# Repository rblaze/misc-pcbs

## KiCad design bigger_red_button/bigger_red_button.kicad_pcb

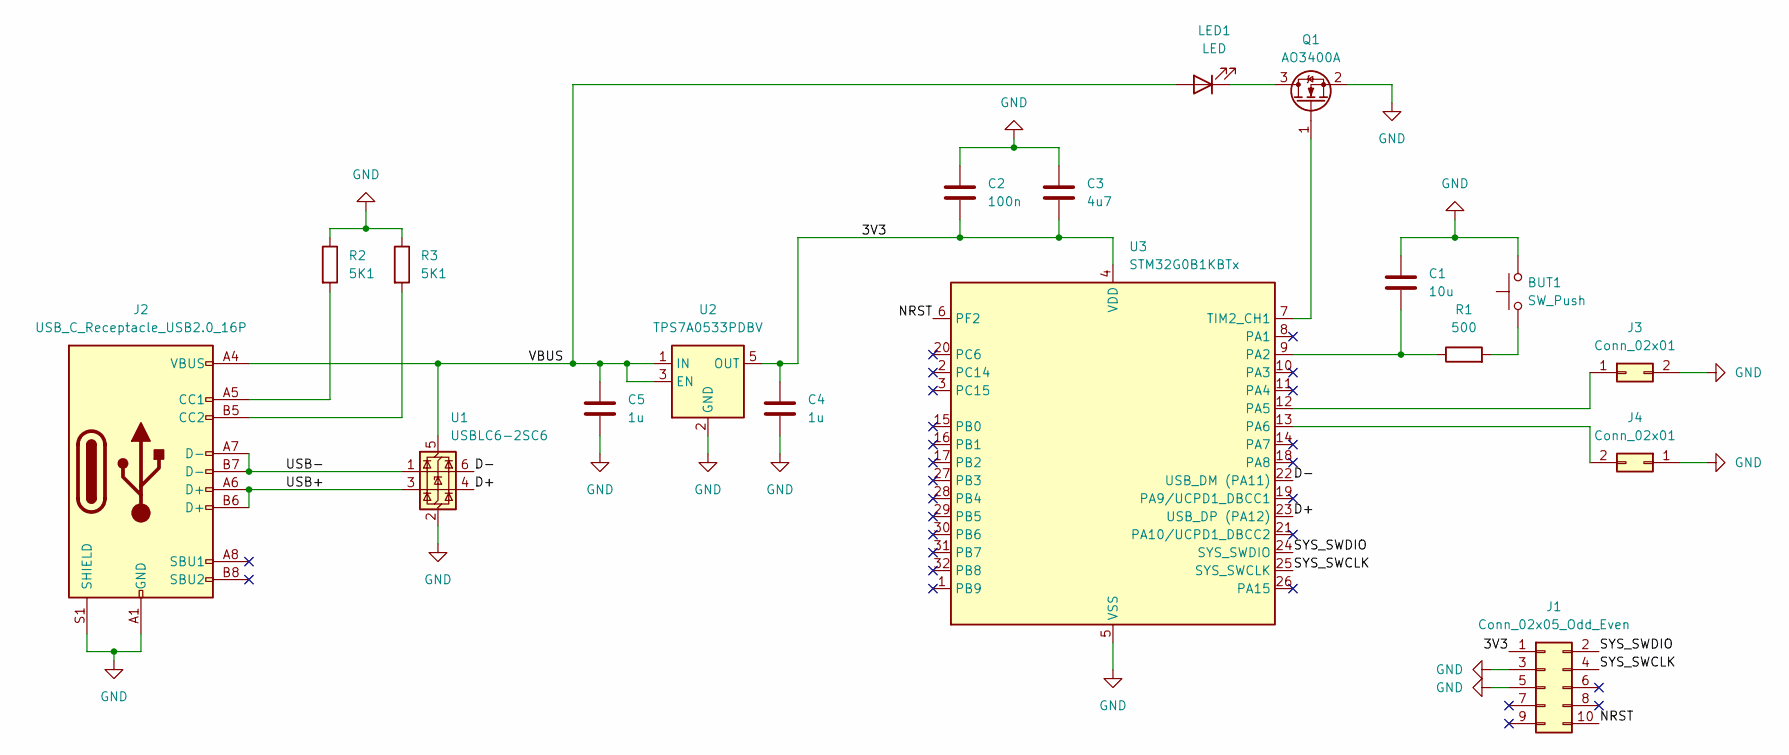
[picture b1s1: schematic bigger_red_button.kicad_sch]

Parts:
BUT1: SW_Push; PinHeader_1x02_P2.54mm_Vertical
C1: 10u; C_0402_1005Metric; LCSC Part # C15525
C2: 100n; C_0402_1005Metric; LCSC Part # C1525
C3: 4u7; C_0402_1005Metric; LCSC Part # C23733
C4, C5: 1u; C_0402_1005Metric; LCSC Part # C52923
J1: Conn_02x05_Odd_Even; SAMTEC_FTSH-105-XX-X-DV; LCSC Part # C448647
J2: USB_C_Receptacle_USB2.0_16P; USB_C_Receptacle_GCT_USB4105-xx-A_16P_TopMnt_Horizontal; LCSC Part # C165948
J3, J4: Conn_02x01; PinHeader_1x02_P2.54mm_Vertical
LED1: LED; PinHeader_1x02_P2.54mm_Vertical
Q1: AO3400A; SOT-23; LCSC Part # C22469448
R1: 500; R_0402_1005Metric; LCSC Part # C25123
R2, R3: 5K1; R_0402_1005Metric; LCSC Part # C25905
U1: USBLC6-2SC6; SOT-23-6; LCSC Part # C7519
U2: TPS7A0533PDBV; SOT-23-5; LCSC Part # C2862740
U3: STM32G0B1KBTx; LQFP-32_7x7mm_P0.8mm; LCSC Part # C3223248

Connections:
/3V3: C2.2, C3.2, C4.1, J1.1, U2.5 (OUT), U3.4 (VDD)
/D+: U1.4 (I/O2), U3.23 (USB_DP (PA12))
/D-: U1.6 (I/O1), U3.22 (USB_DM (PA11))
/NRST: J1.10, U3.6 (PF2)
/SYS_SWCLK: J1.4, U3.25 (SYS_SWCLK)
/SYS_SWDIO: J1.2, U3.24 (SYS_SWDIO)
/USB+: J2.A6 (D+), J2.B6 (D+), U1.3 (I/O2)
/USB-: J2.A7 (D-), J2.B7 (D-), U1.1 (I/O1)
/VBUS: C5.1, J2.A4 (VBUS), J2.A9 (VBUS), J2.B4 (VBUS), J2.B9 (VBUS), LED1.2 (A), U1.5 (VBUS), U2.1 (IN), U2.3 (EN)
GND: BUT1.2, C1.1, C2.1, C3.1, C4.2, C5.2, J1.3, J1.5, J2.A1 (GND), J2.A12 (GND), J2.B1 (GND), J2.B12 (GND), J2.S1 (SHIELD), J3.2, J4.1, Q1.2 (S), R2.1, R3.1, U1.2 (GND), U2.2 (GND), U3.5 (VSS)
unnamed: BUT1.1, R1.2
unnamed: J2.A5 (CC1), R2.2
unnamed: J2.B5 (CC2), R3.2
unnamed: J3.1, U3.12 (PA5)
unnamed: J4.2, U3.13 (PA6)
unnamed: LED1.1 (K), Q1.3 (D)
unnamed: Q1.1 (G), U3.7 (TIM2_CH1)
unnamed: C1.2, R1.1, U3.9 (PA2)

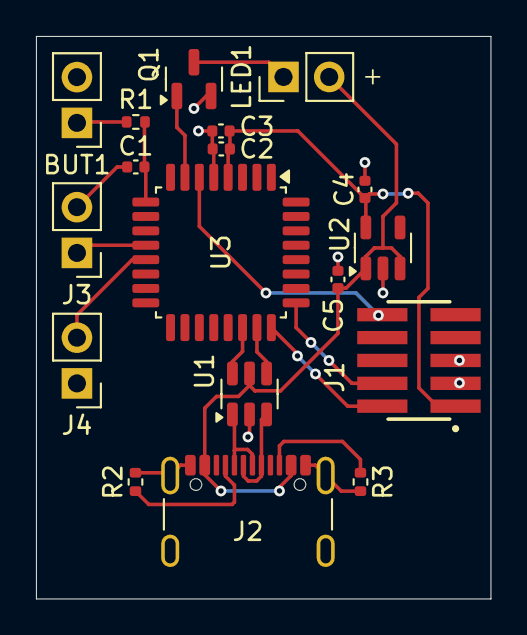
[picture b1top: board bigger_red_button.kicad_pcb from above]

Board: 2 copper layers, 25.2 x 31.2 mm, 18 parts (0 on the bottom side), 18 nets.

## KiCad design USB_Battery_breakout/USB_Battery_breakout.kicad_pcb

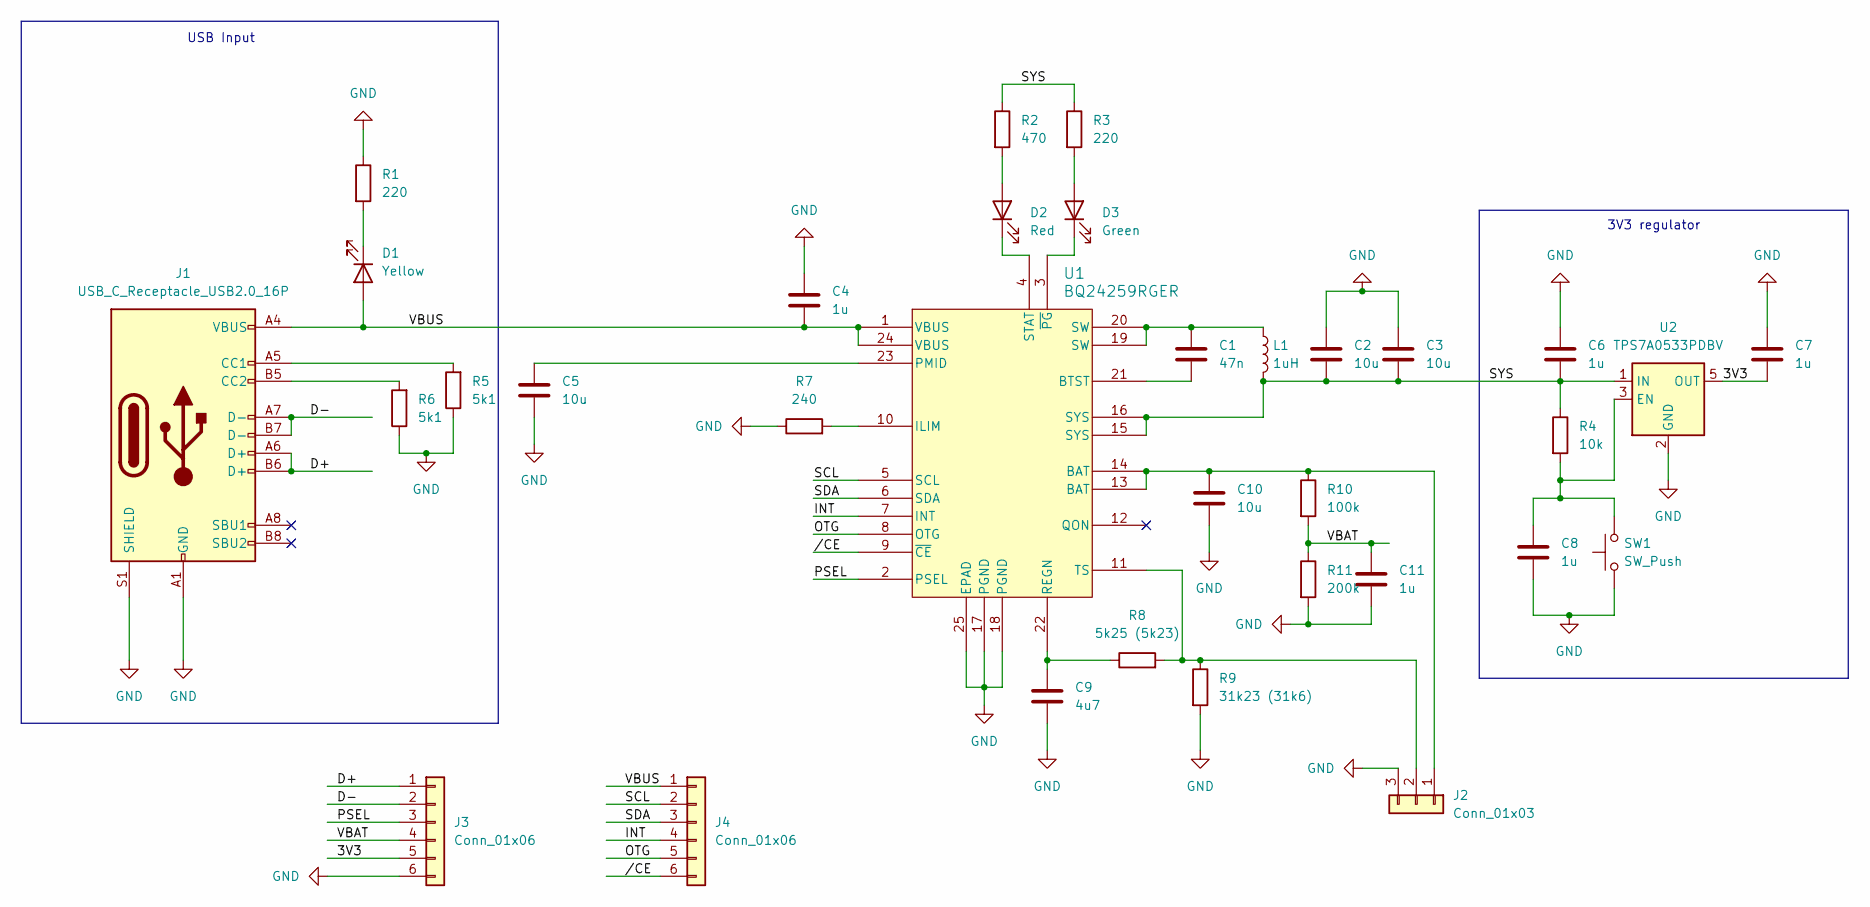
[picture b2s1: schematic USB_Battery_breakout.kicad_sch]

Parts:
C1: 47n; C_0402_1005Metric; JLCPCB C5142571
C2, C3, C5, C10: 10u; C_0603_1608Metric; JLCPCB C19702
C4, C6, C7, C8, C11: 1u; C_0402_1005Metric; JLCPCB C52923
C9: 4u7; C_0402_1005Metric; JLCPCB C23733
D1: Yellow; LED_0603_1608Metric; JLCPCB C72038
D2: Red; LED_0603_1608Metric; JLCPCB C2286
D3: Green; LED_0603_1608Metric; JLCPCB C72043
J1: USB_C_Receptacle_USB2.0_16P; USB_C_Receptacle_GCT_USB4105-xx-A_16P_TopMnt_Horizontal; JLCPCB C165948
J2: Conn_01x03; JST_PH_S3B-PH-SM4-TB_1x03-1MP_P2.00mm_Horizontal
J3, J4: Conn_01x06; PinHeader_1x06_P2.54mm_Vertical
L1: 1uH; L_Murata_DFE201610P; JLCPCB C161082
R1, R3: 220; R_0402_1005Metric; JLCPCB C25091
R2: 470; R_0402_1005Metric; JLCPCB C25117
R4: 10k; R_0402_1005Metric; JLCPCB C25744
R5, R6: 5k1; R_0402_1005Metric; JLCPCB C25905
R7: 240; R_0402_1005Metric; JLCPCB C25091
R8: 5k25 (5k23); R_0402_1005Metric; JLCPCB C852857
R9: 31k23 (31k6); R_0402_1005Metric; JLCPCB C852720
R10: 100k; R_0402_1005Metric; JLCPCB C25741
R11: 200k; R_0402_1005Metric; JLCPCB C25764
SW1: SW_Push; SW_SPST_PTS810
U1: BQ24259RGER; RGE24_2P7X2P7_TEX; JLCPCB C473366
U2: TPS7A0533PDBV; SOT-23-5; JLCPCB C2862740

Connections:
/3V3: C7.2, J3.5, U2.5 (OUT)
/D+: J1.A6 (D+), J1.B6 (D+), J3.1
/D-: J1.A7 (D-), J1.B7 (D-), J3.2
/INT: J4.4, U1.7 (INT)
/OTG: J4.5, U1.8 (OTG)
/PSEL: J3.3, U1.2 (PSEL)
/SCL: J4.2, U1.5 (SCL)
/SDA: J4.3, U1.6 (SDA)
/SYS: C2.2, C3.2, C6.2, L1.2, R2.1, R3.1, R4.1, U1.15 (SYS), U1.16 (SYS), U2.1 (IN)
/VBAT: C11.1, J3.4, R10.2, R11.1
/VBUS: C4.2, D1.2 (A), J1.A4 (VBUS), J1.A9 (VBUS), J1.B4 (VBUS), J1.B9 (VBUS), J4.1, U1.1 (VBUS), U1.24 (VBUS)
//CE: J4.6, U1.9 (~CE)
GND: C2.1, C3.1, C4.1, C5.2, C6.1, C7.1, C8.2, C9.2, C10.2, C11.2, J1.A1 (GND), J1.A12 (GND), J1.B1 (GND), J1.B12 (GND), J1.S1 (SHIELD), J2.3, J3.6, R1.1, R5.1, R6.1, R7.1, R9.2, R11.2, SW1.1, U1.17 (PGND), U1.18 (PGND), U1.25 (EPAD), U1.V, U2.2 (GND)
unnamed: C1.1, L1.1, U1.19 (SW), U1.20 (SW)
unnamed: D1.1 (K), R1.2
unnamed: D2.2 (A), R2.2
unnamed: D2.1 (K), U1.4 (STAT)
unnamed: D3.2 (A), R3.2
unnamed: D3.1 (K), U1.3 (~PG)
unnamed: J1.A5 (CC1), R5.2
unnamed: J1.B5 (CC2), R6.2
unnamed: C10.1, J2.1, R10.1, U1.13 (BAT), U1.14 (BAT)
unnamed: J2.2, R8.2, R9.1, U1.11 (TS)
unnamed: C1.2, U1.21 (BTST)
unnamed: R7.2, U1.10 (ILIM)
unnamed: C5.1, U1.23 (PMID)
unnamed: C9.1, R8.1, U1.22 (REGN)
unnamed: C8.1, R4.2, SW1.2, U2.3 (EN)

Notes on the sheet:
USB Input
3V3 regulator

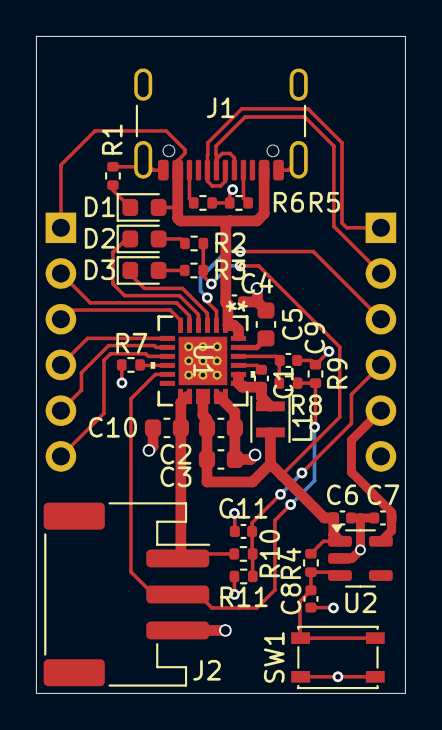
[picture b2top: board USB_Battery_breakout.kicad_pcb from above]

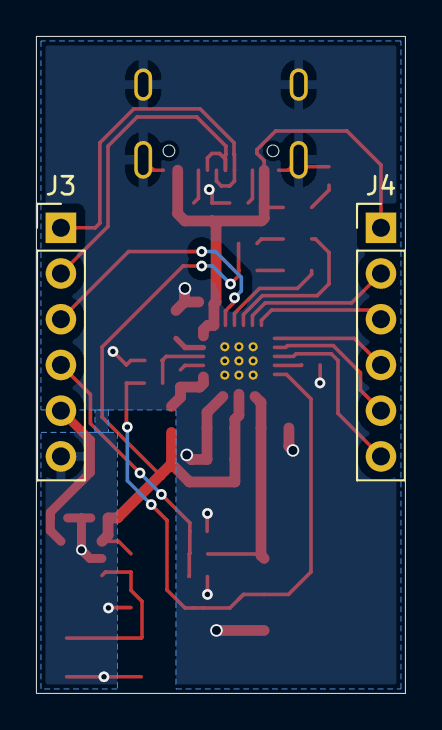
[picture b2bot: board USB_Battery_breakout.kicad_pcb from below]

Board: 2 copper layers, 20.5 x 36.5 mm, 33 parts (2 on the bottom side), 28 nets.

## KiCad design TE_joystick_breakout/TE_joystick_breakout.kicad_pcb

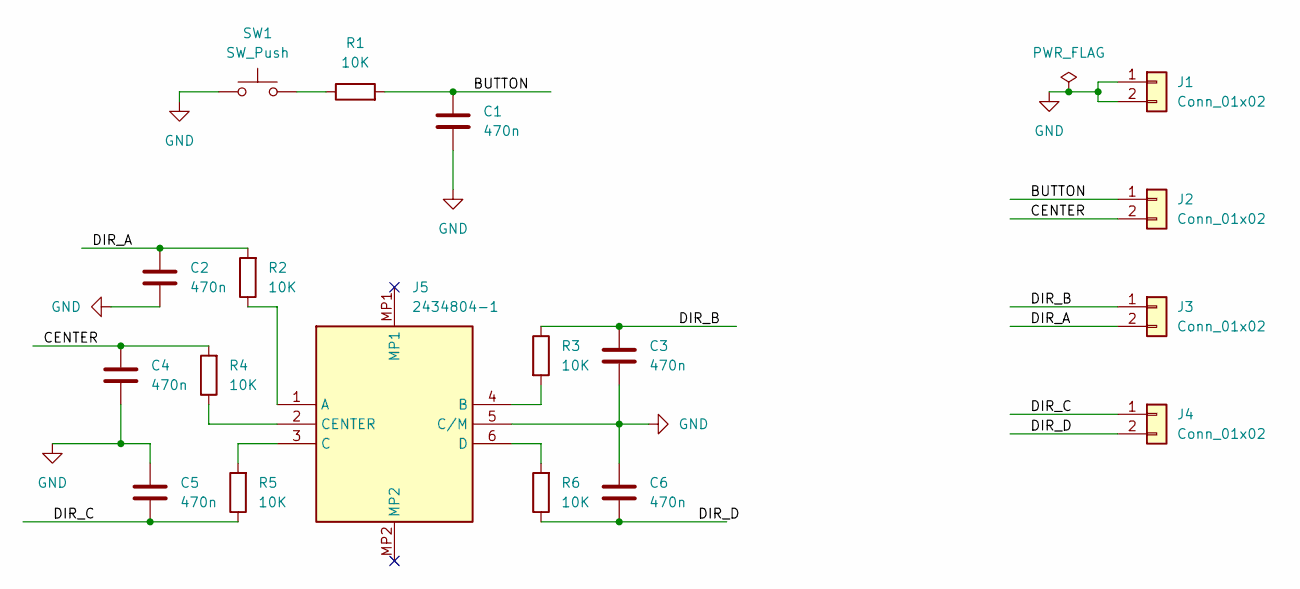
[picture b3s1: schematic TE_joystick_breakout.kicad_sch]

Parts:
C1, C2, C3, C4, C5, C6: 470n; C_0402_1005Metric
J1, J2, J3, J4: Conn_01x02; PinHeader_1x02_P2.54mm_Vertical
J5: 2434804-1; TE_24348041; Manufacturer_Part_Number 2434804-1
R1, R2, R3, R4, R5, R6: 10K; R_0402_1005Metric
SW1: SW_Push; SW_SPST_PTS810

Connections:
/BUTTON: C1.1, J2.1, R1.2
/CENTER: C4.2, J2.2, R4.2
/DIR_A: C2.2, J3.2, R2.2
/DIR_B: C3.2, J3.1, R3.1
/DIR_C: C5.1, J4.1, R5.1
/DIR_D: C6.1, J4.2, R6.1
GND: C1.2, C2.1, C3.1, C4.1, C5.2, C6.2, J1.1, J1.2, J5.5 (C/M), SW1.1
unnamed: J5.1 (A), R2.1
unnamed: J5.4 (B), R3.2
unnamed: J5.3 (C), R5.2
unnamed: J5.2 (CENTER), R4.1
unnamed: J5.6 (D), R6.2
unnamed: R1.1, SW1.2

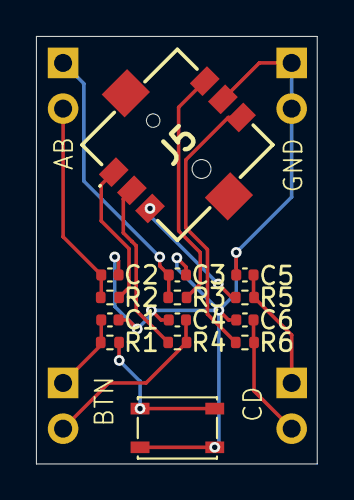
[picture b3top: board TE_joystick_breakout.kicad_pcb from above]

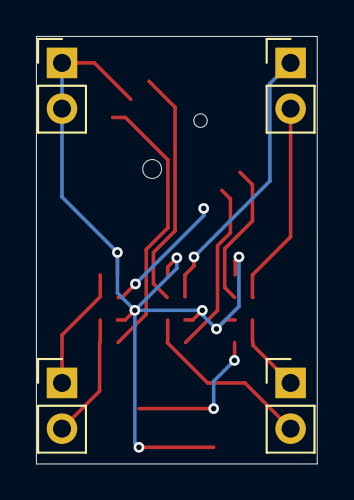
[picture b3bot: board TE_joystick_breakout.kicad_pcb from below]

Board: 2 copper layers, 15.6 x 23.8 mm, 18 parts (4 on the bottom side), 13 nets.

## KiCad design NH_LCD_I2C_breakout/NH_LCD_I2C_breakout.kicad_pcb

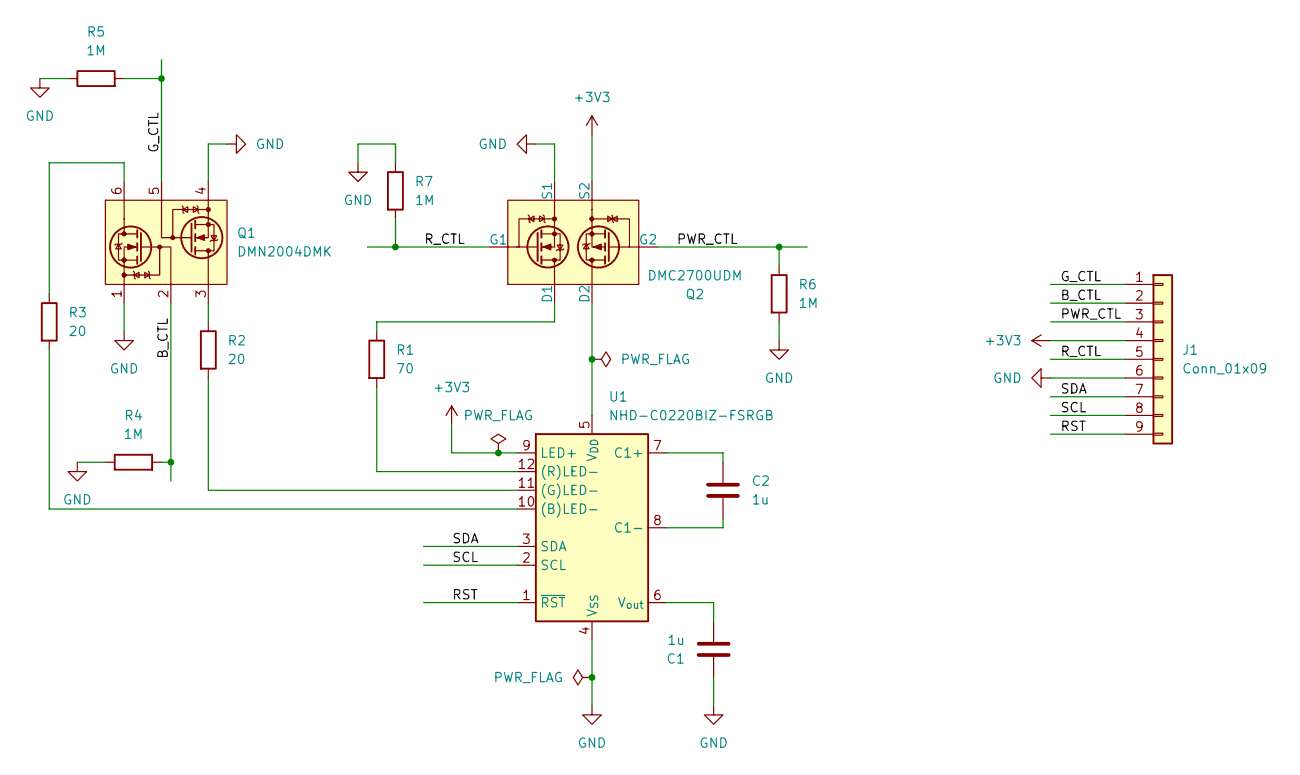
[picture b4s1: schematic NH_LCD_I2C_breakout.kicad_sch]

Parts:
C1, C2: 1u; C_0402_1005Metric
J1: Conn_01x09; PinHeader_1x09_P2.54mm_Vertical
Q1: DMN2004DMK; SOT-23-6
Q2: DMC2700UDM; SOT-23-6
R1: 70; R_0402_1005Metric
R2, R3: 20; R_0402_1005Metric
R4, R5, R6, R7: 1M; R_0402_1005Metric
U1: NHD-C0220BIZ-FSRGB; NHD-C0220BiZ-FSRGB

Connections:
+3V3: J1.4, Q2.2 (S2), U1.9 (LED+)
/B_CTL: J1.2, Q1.2 (G1), R4.2
/G_CTL: J1.1, Q1.5 (G2), R5.2
/PWR_CTL: J1.3, Q2.3 (G2), R6.1
/RST: J1.9, U1.1 (~RST)
/R_CTL: J1.5, Q2.1 (G1), R7.2
/SCL: J1.8, U1.2 (SCL)
/SDA: J1.7, U1.3 (SDA)
GND: C1.1, J1.6, Q1.1 (S1), Q1.4 (S2), Q2.5 (S1), R4.1, R5.1, R6.2, R7.1, U1.4 (V_{SS})
unnamed: Q1.6 (D1), R3.1
unnamed: Q1.3 (D2), R2.1
unnamed: Q2.6 (D1), R1.1
unnamed: Q2.4 (D2), U1.5 (V_{DD})
unnamed: R3.2, U1.10 ((B)LED-)
unnamed: R2.2, U1.11 ((G)LED-)
unnamed: R1.2, U1.12 ((R)LED-)
unnamed: C2.1, U1.7 (C1+)
unnamed: C2.2, U1.8 (C1-)
unnamed: C1.2, U1.6 (V_{out})

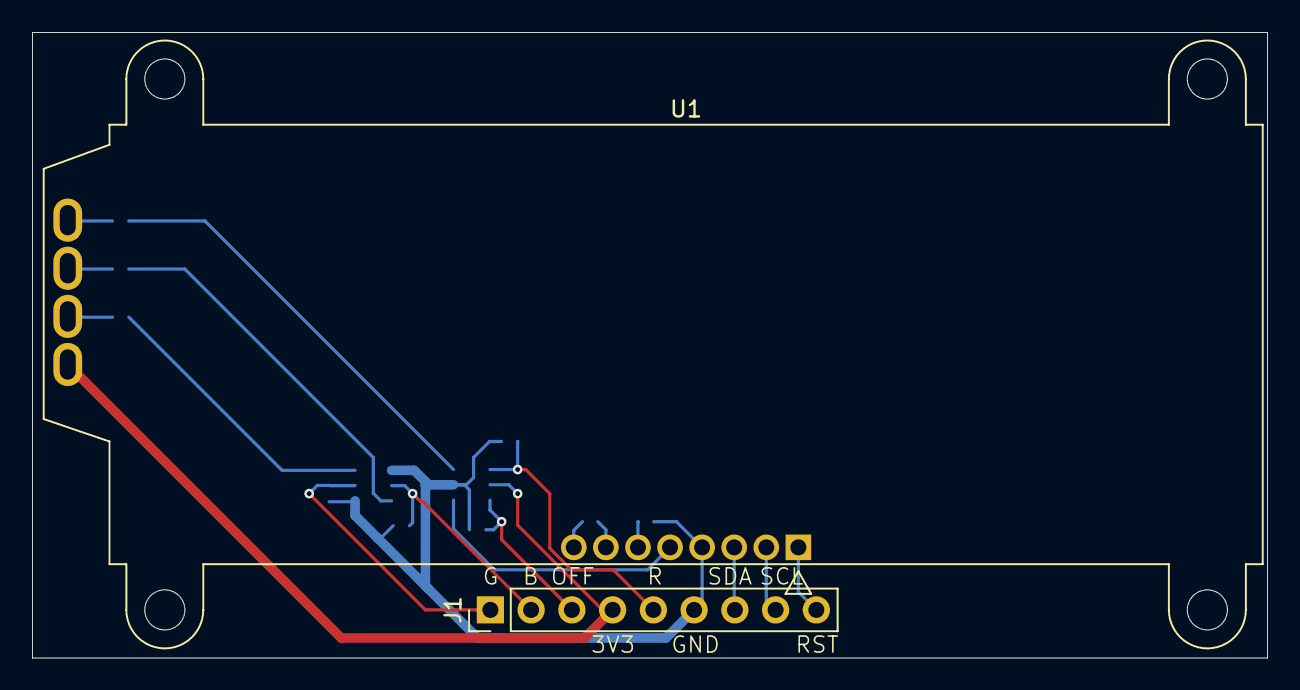
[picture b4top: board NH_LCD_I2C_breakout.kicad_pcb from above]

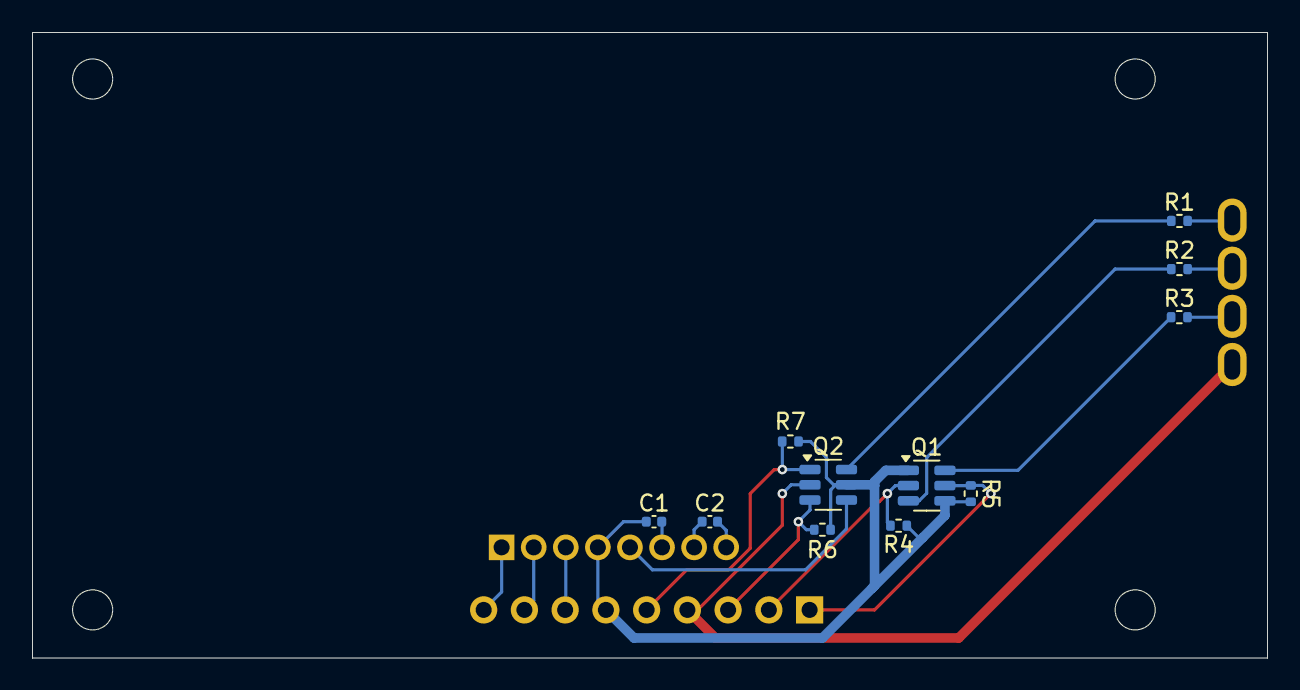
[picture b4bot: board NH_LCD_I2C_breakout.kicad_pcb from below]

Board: 2 copper layers, 77.0 x 39.0 mm, 13 parts (11 on the bottom side), 19 nets.

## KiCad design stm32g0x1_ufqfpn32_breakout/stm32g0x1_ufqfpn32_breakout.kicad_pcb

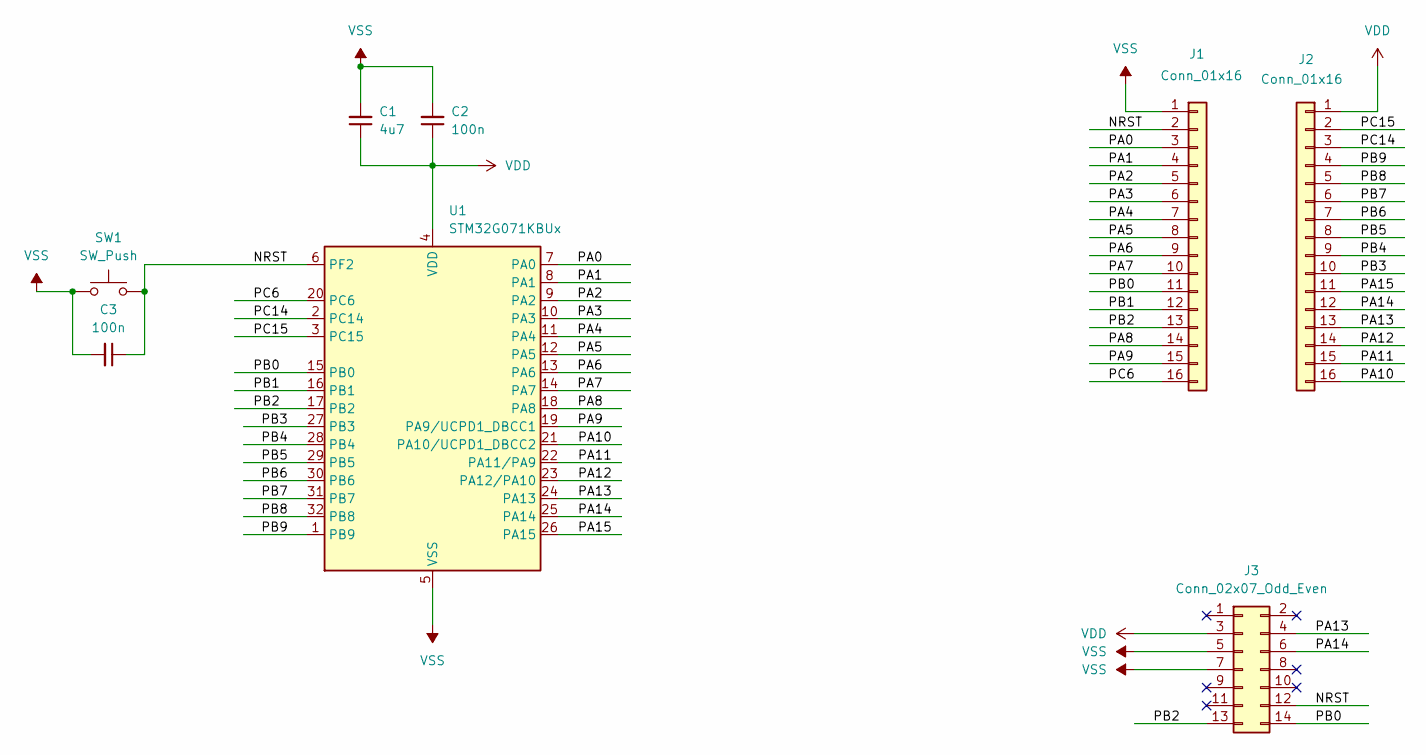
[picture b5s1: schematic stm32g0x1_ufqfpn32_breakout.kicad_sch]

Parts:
C1: 4u7; C_0402_1005Metric
C2, C3: 100n; C_0402_1005Metric
J1, J2: Conn_01x16; PinHeader_1x16_P2.54mm_Vertical
J3: Conn_02x07_Odd_Even; SAMTEC_FTSH-107-01-L-DV-K-A
SW1: SW_Push; SW_SPST_PTS810
U1: STM32G071KBUx; QFN-32-1EP_5x5mm_P0.5mm_EP3.45x3.45mm

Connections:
/NRST: C3.1, J1.2, J3.12, SW1.2, U1.6 (PF2)
/PA0: J1.3, U1.7 (PA0)
/PA1: J1.4, U1.8 (PA1)
/PA2: J1.5, U1.9 (PA2)
/PA3: J1.6, U1.10 (PA3)
/PA4: J1.7, U1.11 (PA4)
/PA5: J1.8, U1.12 (PA5)
/PA6: J1.9, U1.13 (PA6)
/PA7: J1.10, U1.14 (PA7)
/PA8: J1.14, U1.18 (PA8)
/PA9: J1.15, U1.19 (PA9/UCPD1_DBCC1)
/PA10: J2.16, U1.21 (PA10/UCPD1_DBCC2)
/PA11: J2.15, U1.22 (PA11/PA9)
/PA12: J2.14, U1.23 (PA12/PA10)
/PA13: J2.13, J3.4, U1.24 (PA13)
/PA14: J2.12, J3.6, U1.25 (PA14)
/PA15: J2.11, U1.26 (PA15)
/PB0: J1.11, J3.14, U1.15 (PB0)
/PB1: J1.12, U1.16 (PB1)
/PB2: J1.13, J3.13, U1.17 (PB2)
/PB3: J2.10, U1.27 (PB3)
/PB4: J2.9, U1.28 (PB4)
/PB5: J2.8, U1.29 (PB5)
/PB6: J2.7, U1.30 (PB6)
/PB7: J2.6, U1.31 (PB7)
/PB8: J2.5, U1.32 (PB8)
/PB9: J2.4, U1.1 (PB9)
/PC6: J1.16, U1.20 (PC6)
/PC14: J2.3, U1.2 (PC14)
/PC15: J2.2, U1.3 (PC15)
VDD: C1.1, C2.1, J2.1, J3.3, U1.4 (VDD)
VSS: C1.2, C2.2, C3.2, J1.1, J3.5, J3.7, SW1.1, U1.5 (VSS), U1.33 (VSS)

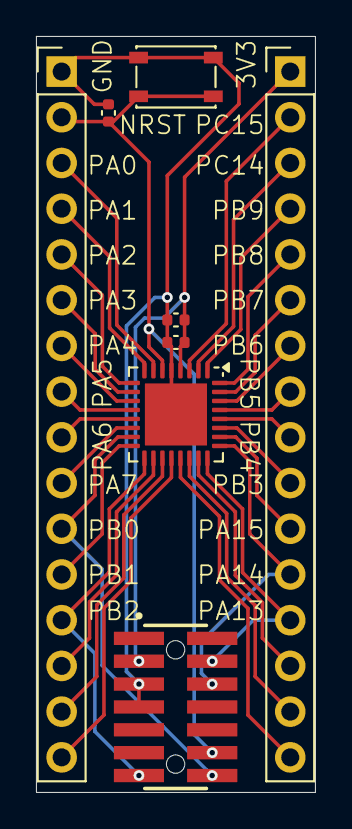
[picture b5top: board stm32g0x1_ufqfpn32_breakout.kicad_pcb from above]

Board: 2 copper layers, 15.5 x 42.0 mm, 8 parts (0 on the bottom side), 32 nets.

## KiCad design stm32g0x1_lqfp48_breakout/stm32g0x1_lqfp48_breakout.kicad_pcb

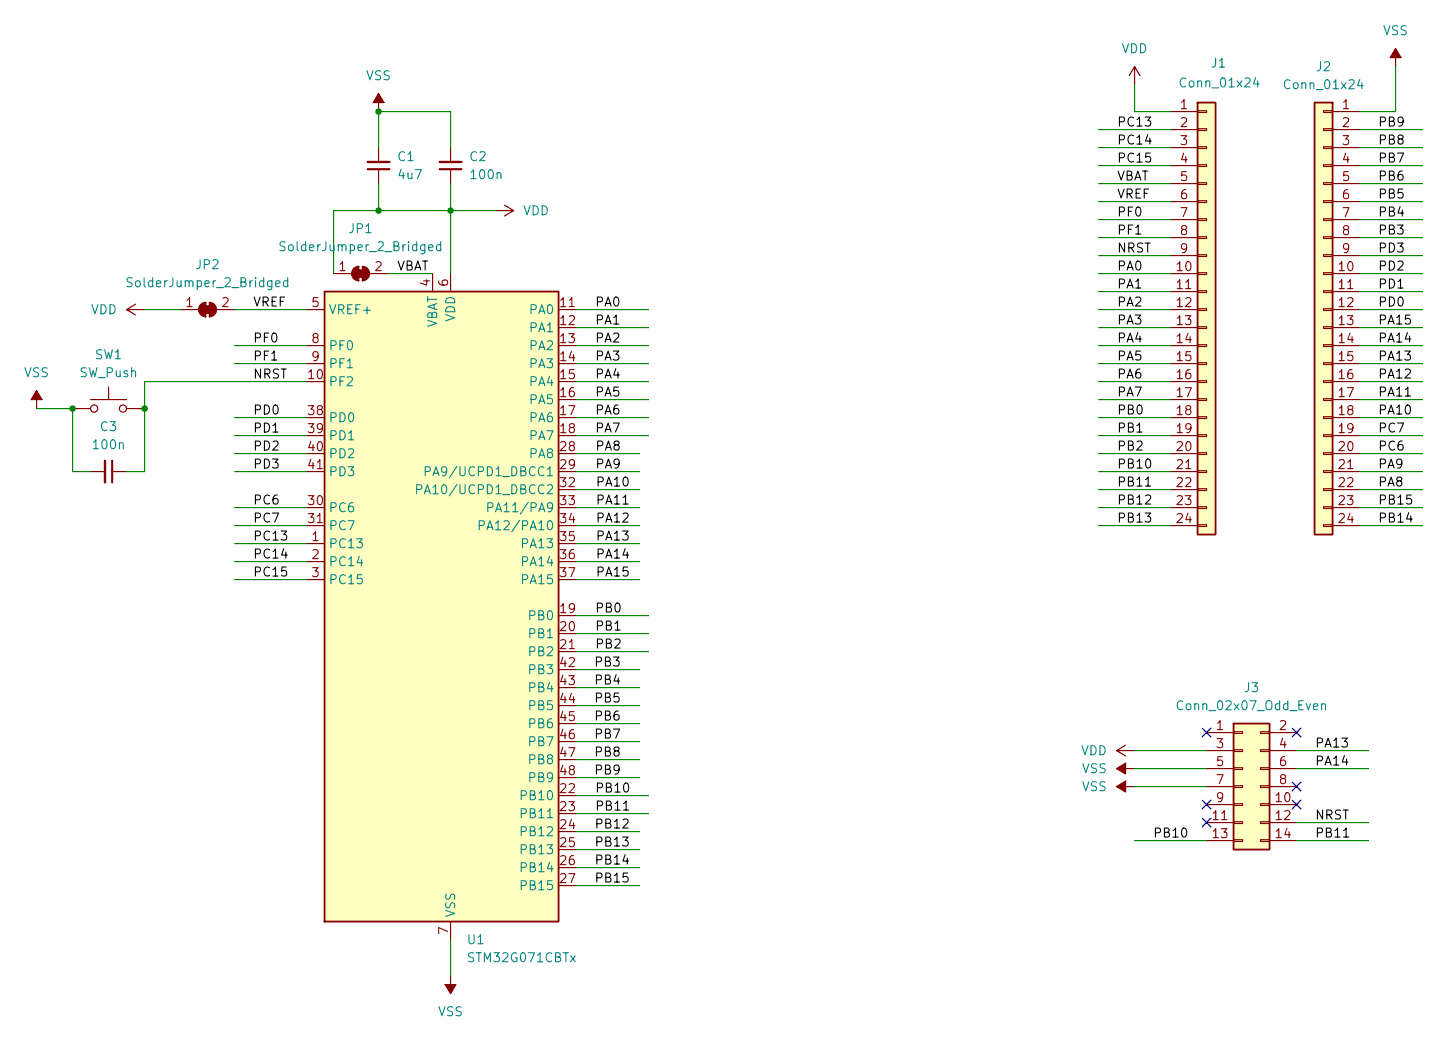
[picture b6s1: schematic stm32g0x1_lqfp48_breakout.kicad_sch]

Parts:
C1: 4u7; C_0402_1005Metric
C2, C3: 100n; C_0402_1005Metric
J1, J2: Conn_01x24; PinHeader_1x24_P2.54mm_Vertical
J3: Conn_02x07_Odd_Even; SAMTEC_FTSH-107-01-L-DV-K-A
JP1, JP2: SolderJumper_2_Bridged; SolderJumper-2_P1.3mm_Open_TrianglePad1.0x1.5mm
SW1: SW_Push; SW_SPST_PTS810
U1: STM32G071CBTx; LQFP-48_7x7mm_P0.5mm

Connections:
/NRST: C3.1, J1.9, J3.12, SW1.2, U1.10 (PF2)
/PA0: J1.10, U1.11 (PA0)
/PA1: J1.11, U1.12 (PA1)
/PA2: J1.12, U1.13 (PA2)
/PA3: J1.13, U1.14 (PA3)
/PA4: J1.14, U1.15 (PA4)
/PA5: J1.15, U1.16 (PA5)
/PA6: J1.16, U1.17 (PA6)
/PA7: J1.17, U1.18 (PA7)
/PA8: J2.22, U1.28 (PA8)
/PA9: J2.21, U1.29 (PA9/UCPD1_DBCC1)
/PA10: J2.18, U1.32 (PA10/UCPD1_DBCC2)
/PA11: J2.17, U1.33 (PA11/PA9)
/PA12: J2.16, U1.34 (PA12/PA10)
/PA13: J2.15, J3.4, U1.35 (PA13)
/PA14: J2.14, J3.6, U1.36 (PA14)
/PA15: J2.13, U1.37 (PA15)
/PB0: J1.18, U1.19 (PB0)
/PB1: J1.19, U1.20 (PB1)
/PB2: J1.20, U1.21 (PB2)
/PB3: J2.8, U1.42 (PB3)
/PB4: J2.7, U1.43 (PB4)
/PB5: J2.6, U1.44 (PB5)
/PB6: J2.5, U1.45 (PB6)
/PB7: J2.4, U1.46 (PB7)
/PB8: J2.3, U1.47 (PB8)
/PB9: J2.2, U1.48 (PB9)
/PB10: J1.21, J3.13, U1.22 (PB10)
/PB11: J1.22, J3.14, U1.23 (PB11)
/PB12: J1.23, U1.24 (PB12)
/PB13: J1.24, U1.25 (PB13)
/PB14: J2.24, U1.26 (PB14)
/PB15: J2.23, U1.27 (PB15)
/PC6: J2.20, U1.30 (PC6)
/PC7: J2.19, U1.31 (PC7)
/PC13: J1.2, U1.1 (PC13)
/PC14: J1.3, U1.2 (PC14)
/PC15: J1.4, U1.3 (PC15)
/PD0: J2.12, U1.38 (PD0)
/PD1: J2.11, U1.39 (PD1)
/PD2: J2.10, U1.40 (PD2)
/PD3: J2.9, U1.41 (PD3)
/PF0: J1.7, U1.8 (PF0)
/PF1: J1.8, U1.9 (PF1)
/VBAT: J1.5, JP1.2 (B), U1.4 (VBAT)
/VREF: J1.6, JP2.2 (B), U1.5 (VREF+)
VDD: C1.1, C2.1, J1.1, J3.3, JP1.1 (A), JP2.1 (A), U1.6 (VDD)
VSS: C1.2, C2.2, C3.2, J2.1, J3.5, J3.7, SW1.1, U1.7 (VSS)

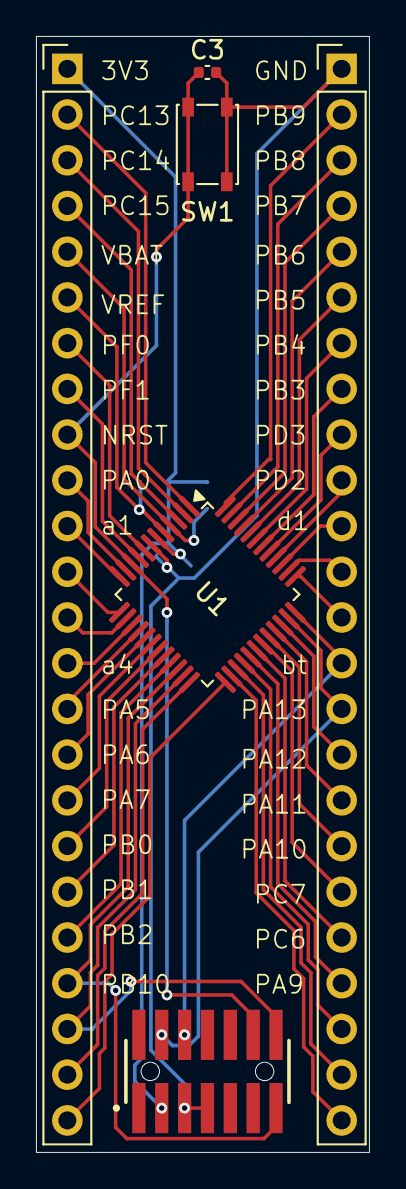
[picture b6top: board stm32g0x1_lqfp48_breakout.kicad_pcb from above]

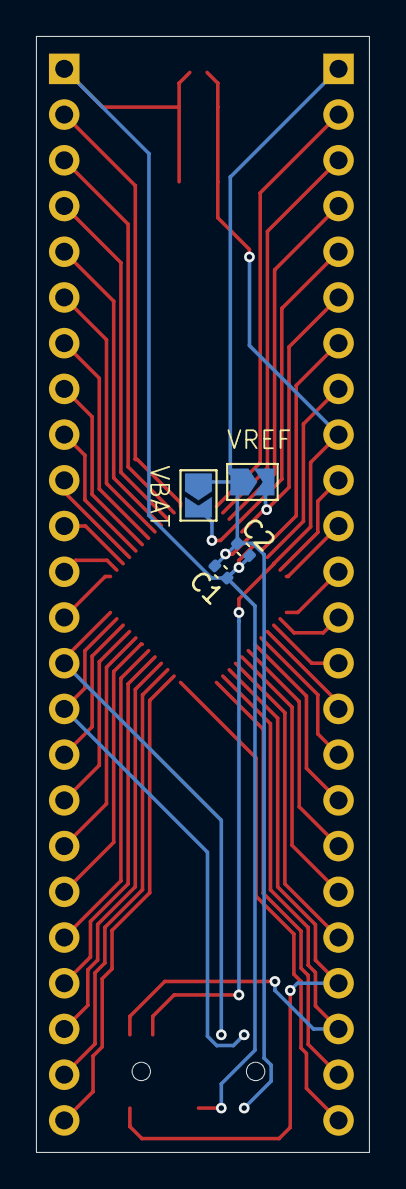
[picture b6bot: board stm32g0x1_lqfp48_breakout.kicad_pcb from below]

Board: 2 copper layers, 18.5 x 62.0 mm, 10 parts (4 on the bottom side), 48 nets.

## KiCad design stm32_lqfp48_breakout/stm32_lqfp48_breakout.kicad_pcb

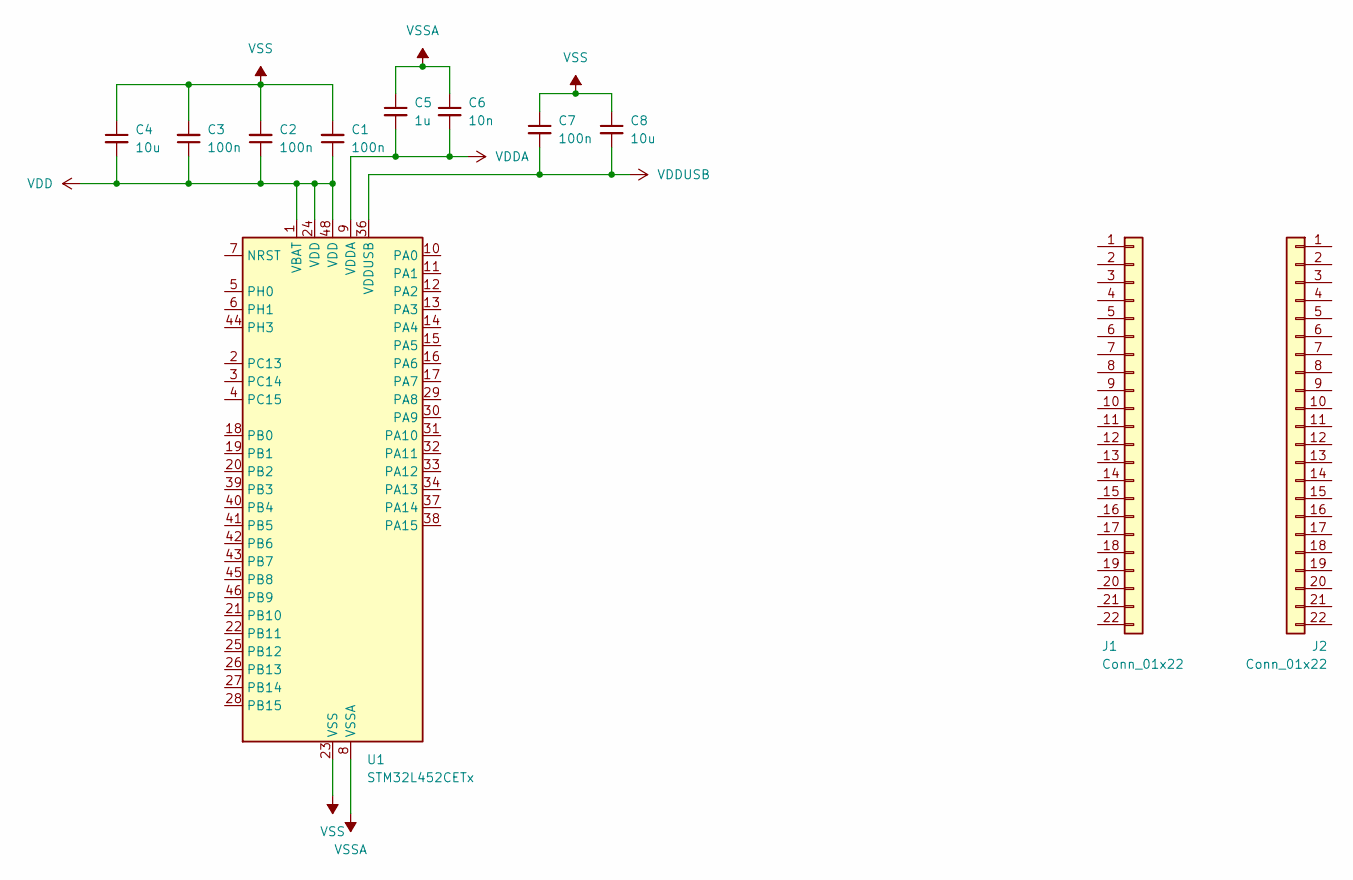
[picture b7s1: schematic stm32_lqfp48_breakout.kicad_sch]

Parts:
C1, C2, C3, C7: 100n; C_0402_1005Metric
C4, C8: 10u; C_0402_1005Metric
C5: 1u; C_0402_1005Metric
C6: 10n; C_0402_1005Metric
J1, J2: Conn_01x22
U1: STM32L452CETx; LQFP-48_7x7mm_P0.5mm

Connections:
/NRST: J1.7, U1.7 (NRST)
/PA0: J1.10, U1.10 (PA0)
/PA1: J1.11, U1.11 (PA1)
/PA2: J1.12, U1.12 (PA2)
/PA3: J1.13, U1.13 (PA3)
/PA4: J1.14, U1.14 (PA4)
/PA5: J1.15, U1.15 (PA5)
/PA6: J1.16, U1.16 (PA6)
/PA7: J1.17, U1.17 (PA7)
/PA8: J2.18, U1.29 (PA8)
/PA9: J2.17, U1.30 (PA9)
/PA10: J2.16, U1.31 (PA10)
/PA11: J2.15, U1.32 (PA11)
/PA12: J2.14, U1.33 (PA12)
/PA13: J2.13, U1.34 (PA13)
/PA14: J2.11, U1.37 (PA14)
/PA15: J2.10, U1.38 (PA15)
/PB0: J1.18, U1.18 (PB0)
/PB1: J1.19, U1.19 (PB1)
/PB2: J1.20, U1.20 (PB2)
/PB3: J2.9, U1.39 (PB3)
/PB4: J2.8, U1.40 (PB4)
/PB5: J2.7, U1.41 (PB5)
/PB6: J2.6, U1.42 (PB6)
/PB7: J2.5, U1.43 (PB7)
/PB8: J2.3, U1.45 (PB8)
/PB9: J2.2, U1.46 (PB9)
/PB10: J1.21, U1.21 (PB10)
/PB11: J1.22, U1.22 (PB11)
/PB12: J2.22, U1.25 (PB12)
/PB13: J2.21, U1.26 (PB13)
/PB14: J2.20, U1.27 (PB14)
/PB15: J2.19, U1.28 (PB15)
/PC13: J1.2, U1.2 (PC13)
/PC14: J1.3, U1.3 (PC14)
/PC15: J1.4, U1.4 (PC15)
/PH0: J1.5, U1.5 (PH0)
/PH1: J1.6, U1.6 (PH1)
/PH3: J2.4, U1.44 (PH3)
VDD: C1.1, C2.1, C3.1, C4.2, J1.1, U1.1 (VBAT), U1.24 (VDD), U1.48 (VDD)
VDDA: C5.2, C6.2, J1.9, U1.9 (VDDA)
VDDUSB: C7.2, C8.2, J2.12, U1.36 (VDDUSB)
VSS: C1.2, C2.2, C3.2, C4.1, C7.1, C8.1, J2.1, U1.23 (VSS), U1.35 (VSS), U1.47 (VSS)
VSSA: C5.1, C6.1, J1.8, U1.8 (VSSA)

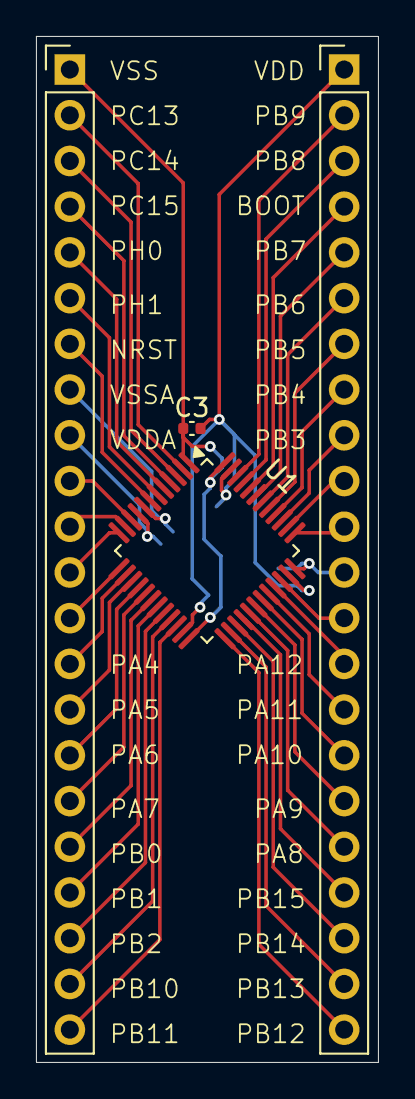
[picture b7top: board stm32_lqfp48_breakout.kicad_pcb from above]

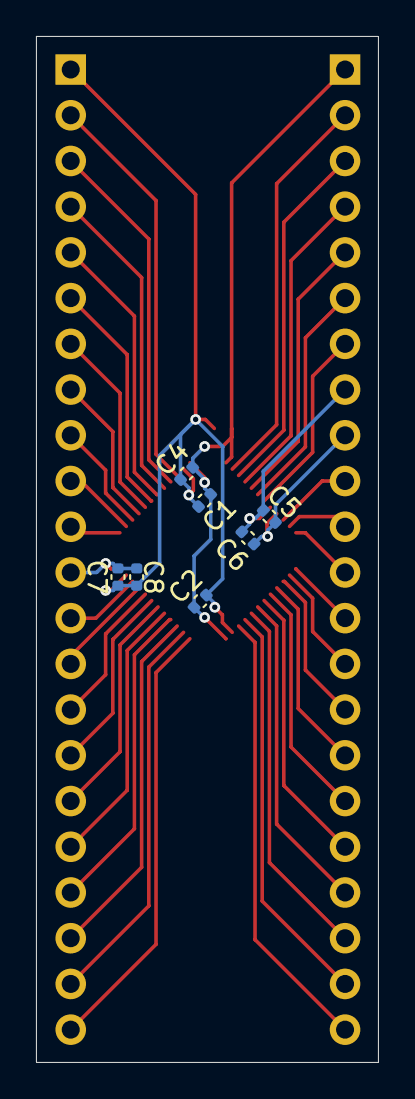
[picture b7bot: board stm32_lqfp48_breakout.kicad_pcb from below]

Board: 2 copper layers, 19.0 x 57.0 mm, 11 parts (7 on the bottom side), 44 nets.

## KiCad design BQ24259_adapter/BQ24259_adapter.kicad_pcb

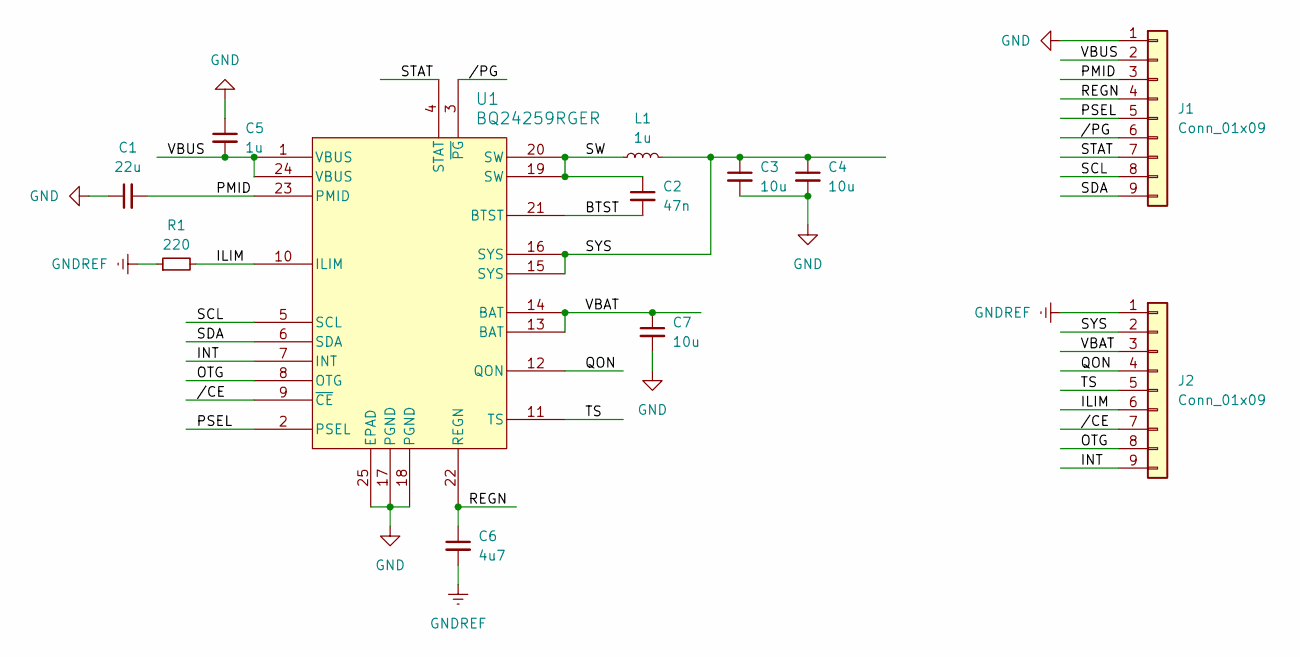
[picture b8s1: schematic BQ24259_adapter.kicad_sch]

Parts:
C1: 22u; C_0603_1608Metric
C2: 47n; C_0402_1005Metric
C3, C4: 10u; C_0402_1005Metric
C5: 1u; C_0402_1005Metric
C6: 4u7; C_0402_1005Metric
C7: 10u; C_0603_1608Metric
J1, J2: Conn_01x09; PinHeader_1x09_P2.54mm_Vertical
L1: 1u; L_Murata_DFE201610P
R1: 220; R_0402_1005Metric
U1: BQ24259RGER; RGE24_2P7X2P7_TEX

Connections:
/BTST: C2.2, U1.21 (BTST)
/ILIM: J2.6, R1.2, U1.10 (ILIM)
/INT: J2.9, U1.7 (INT)
/OTG: J2.8, U1.8 (OTG)
/PMID: C1.2, J1.3, U1.23 (PMID)
/PSEL: J1.5, U1.2 (PSEL)
/QON: J2.4, U1.12 (QON)
/REGN: C6.1, J1.4, U1.22 (REGN)
/SCL: J1.8, U1.5 (SCL)
/SDA: J1.9, U1.6 (SDA)
/STAT: J1.7, U1.4 (STAT)
/SW: C2.1, L1.1, U1.19 (SW), U1.20 (SW)
/SYS: C3.1, C4.1, J2.2, L1.2, U1.15 (SYS), U1.16 (SYS)
/TS: J2.5, U1.11 (TS)
/VBAT: C7.1, J2.3, U1.13 (BAT), U1.14 (BAT)
/VBUS: C5.2, J1.2, U1.1 (VBUS), U1.24 (VBUS)
//CE: J2.7, U1.9 (~CE)
//PG: J1.6, U1.3 (~PG)
GND: C1.1, C3.2, C4.2, C5.1, C7.2, J1.1, U1.17 (PGND), U1.18 (PGND), U1.25 (EPAD), U1.V
GNDREF: C6.2, J2.1, R1.1
